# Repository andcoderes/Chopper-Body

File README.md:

# Chopper Body V2

## Acknowledgments

This firmware was strongly influenced by the [Amidala](https://github.com/thePunderWoman/Amidala) firmware by [thePunderWoman](https://github.com/thePunderWoman).

ESP32-based body controller for the Chopper robot. Controls drive motors, dome rotation, body servos, MP3 audio, and a bubble machine via ESP-NOW commands from the controller.

## Features

- **MDDS30 drive motors** — PWM Independent mode, differential steering
- **Cytron MD10C dome rotation** — bidirectional speed control
- **Pololu Maestro servos** — scripted body animations via Serial1
- **MP3 audio player** — serial protocol playback via Serial2
- **Bubbles relay** — on/off control
- **ESP-NOW** — encrypted communication with the controller
- **WiFi AP + OTA** — web interface at `chopper.body` for firmware updates
- **Safety timeout** — motors stop after 500ms without commands or on ESP-NOW disconnect

## ESP32 Pin Assignments

| Function | GPIO | Type | Notes |
|---|---|---|---|
| **MDDS30 IN1** (left dir) | 4 | Digital out | LOW = forward, HIGH = reverse. 10k pull-down on board |
| **MDDS30 AN1** (left speed) | 17 | LEDC PWM | 5 kHz, 8-bit. 10k pull-down on board |
| **MDDS30 IN2** (right dir) | 16 | Digital out | LOW = forward, HIGH = reverse. 10k pull-down on board |
| **MDDS30 AN2** (right speed) | 5 | LEDC PWM | 5 kHz, 8-bit. 10k pull-down on board |
| **Cytron MD10C DIR** (dome dir) | 14 | Digital out | 10k pull-down on board |
| **Cytron MD10C PWM** (dome speed) | 27 | LEDC PWM | 5 kHz, 8-bit. 10k pull-down on board |
| **Dome home sensor** | 26 | Digital in | A3144 hall-effect, 10k+20k divider |
| **Dome encoder A** | 25 | Digital in | 10k+20k divider |
| **Dome encoder B** | 33 | Digital in | 10k+20k divider |
| **Pololu Maestro TX** | 32 | Serial1 TX | 9600 baud |
| **Pololu Maestro RX** | 35 | Serial1 RX | Input-only. 1k + 2k voltage divider (5V -> 3.3V) |
| **MP3 Player TX** | 19 | Serial2 TX | 9600 baud |
| **MP3 Player RX** | 18 | Serial2 RX | 1k + 2k voltage divider (5V -> 3.3V) |
| **Bubbles relay** | 21 | Digital out | Relay module, active HIGH |
| **USB Debug TX** | 1 | Serial0 TX | 115200 baud |
| **USB Debug RX** | 3 | Serial0 RX | 115200 baud |

GPIO12 and GPIO13 (previously used for MDDS30) are intentionally left
unconnected — GPIO12 is an ESP32 boot-strapping pin (flash voltage select)
and stray HIGH signals on it during power-up can put the board in a reset
loop. GPIO22/23 (previously Maestro) and GPIO34 (previously dome encoder B)
are also now unused.

### MDDS30 DIP Switch Setting

`0b10110100` — PWM Independent mode. All three hardware UARTs remain free.

### Serial Port Allocation

| UART | GPIO TX | GPIO RX | Baud | Device |
|---|---|---|---|---|
| Serial0 | 1 | 3 | 115200 | USB debug console |
| Serial1 | 32 | 35 | 9600 | Pololu Maestro servo controller |
| Serial2 | 19 | 18 | 9600 | MP3 player module (Catalex-style, requires "select TF card" init) |

## Build

Requires [PlatformIO](https://platformio.org/).

Before your first build, set up ESP-NOW encryption keys — see
[Generating ESP-NOW keys](#generating-esp-now-keys) below. The build will
fail with a clear error if `.env` is missing.

```bash
# One-time setup: copy the template and fill in real keys
cp .env.example .env

# Compile firmware
pio run

# Upload to ESP32
pio run --target upload

# Run unit tests (native)
pio test -e native

# Monitor serial output
pio device monitor
```

## Project Structure

```
pcb/                                  # KiCad project (schematic, board, gerbers)
firmware/
  platformio.ini
  .env.example                       # Template for ESP-NOW keys — copy to .env
  partitions/ota_4MB.csv
  scripts/load_secrets.py            # Pre-build: .env -> include/secrets.h
  scripts/embed_web.py              # Pre-build: inlines CSS into HTML
  web/
    assets/common.css                # Shared styles
    index.html                       # Home page (info + links)
    update.html                      # OTA firmware upload page
  include/
    web_pages.h                      # AUTO-GENERATED by embed_web.py
    secrets.h                        # AUTO-GENERATED by load_secrets.py, gitignored
  src/
    config.h                         # Pin definitions, timeouts (keys come from secrets.h)
    main.cpp                         # Setup/loop, WiFi, command dispatch
    communication/
      MessageTypes.h                 # BodyCommand / BodyTelemetry structs
      EspNowController.h/.cpp        # ESP-NOW encrypted communication
    motor/
      MotorController.h/.cpp         # MDDS30 + L298N motor control
    servo/
      ServoController.h/.cpp         # Pololu Maestro body servos
    audio/
      AudioController.h/.cpp         # Serial MP3 player protocol
    web/
      WebController.h/.cpp           # WiFi AP, OTA updates, info API
      logger.h                       # Serial logging utility
  test/
    mocks/                           # Arduino/ESP32 mock headers
    test_message_types/              # Struct packing and field tests
    test_motor_controller/           # Drive mixing, dome, timeout tests
    test_audio_controller/           # MP3 protocol frame tests
    test_servo_controller/           # Animation state machine tests
    test_esp_now_controller/         # Connection timeout, dispatch tests
```

## ESP-NOW Protocol

### Controller -> Body (msgType = 3, 26 bytes)

| Field | Type | Description |
|---|---|---|
| msgType | int8 | Always 3 |
| status | int8 | 0 = buttons, 1 = movement, 2 = settings, -1 = connection |
| lx | int8 | Drive X axis: -100 to 100 |
| ly | int8 | Drive Y axis: -100 to 100 |
| domeSpeed | int8 | Dome rotation: -100 to 100 |
| audioTrack | uint8 | 0 = none, 1-255 = play track |
| volume | uint8 | 0-30 |
| bubbles | uint8 | 0 = off, 1 = on |
| button | char[8] | Servo button name (e.g. "y", "du") |
| macro | int16[4] | Servo macro IDs |
| connectionStatus | int8 | 0 = disconnected, 1 = connected |
| padding | uint8 | Alignment padding |

### Body -> Controller (msgType = 4, 8 bytes)

| Field | Type | Description |
|---|---|---|
| msgType | int8 | Always 4 |
| connected | uint8 | 1 if ESP-NOW link active |
| motorsActive | uint8 | 1 if drive/dome motors running |
| audioPlaying | uint8 | 1 if audio track playing |
| uptimeMs | uint32 | Milliseconds since boot |

## WiFi Access Point

- **SSID:** ChopperBody
- **IP:** 192.168.5.1
- **mDNS:** chopper-body.local
- **Pages:** `/` (home), `/update` (OTA)
- **API:** `/api/info` (JSON: version, uptime, heap, MAC)

## Generating ESP-NOW keys

This board talks to the other Chopper boards over encrypted ESP-NOW. Before
your first build, generate two 16-byte (128-bit) keys — a Primary Master Key
(PMK) and a Local Master Key (LMK) — and put them in a `.env` file
(gitignored, never commit it) at the project root:

```bash
cp .env.example .env
```

Generate two random 16-byte keys, each as 32 hex characters:

```bash
# Option 1: openssl
openssl rand -hex 16   # run twice — once for PMK_KEY, once for LMK_KEY

# Option 2: python
python3 -c "import secrets; print(secrets.token_hex(16))"
```

Edit `.env` and paste the values in:

```
PMK_KEY=<first random hex string>
LMK_KEY=<second random hex string>
```

**These two keys must be byte-for-byte identical across chopper body,
chopper head, and chopper receiver** — generate them once and copy the same
`.env` values into all three projects. Mismatched keys mean the boards can't
decrypt each other's ESP-NOW packets and the mesh will never connect.

`.env` also holds `CONTROLLER_MAC` — the controller's WiFi MAC address (as
hex, e.g. `C0CDD6CA29E0`), which must likewise be identical across all three
firmware projects — and `WIFI_AP_PASSWORD`, the password for this board's
local OTA-update access point (pick your own, at least 8 characters; unlike
the other values, this one doesn't need to match the other boards).

`scripts/load_secrets.py` runs automatically before every build (see
`platformio.ini`) and turns `.env` into `include/secrets.h`, which
`config.h` includes. Neither `.env` nor the generated `secrets.h` are
committed to git — the build fails with a clear error if `.env` is missing.

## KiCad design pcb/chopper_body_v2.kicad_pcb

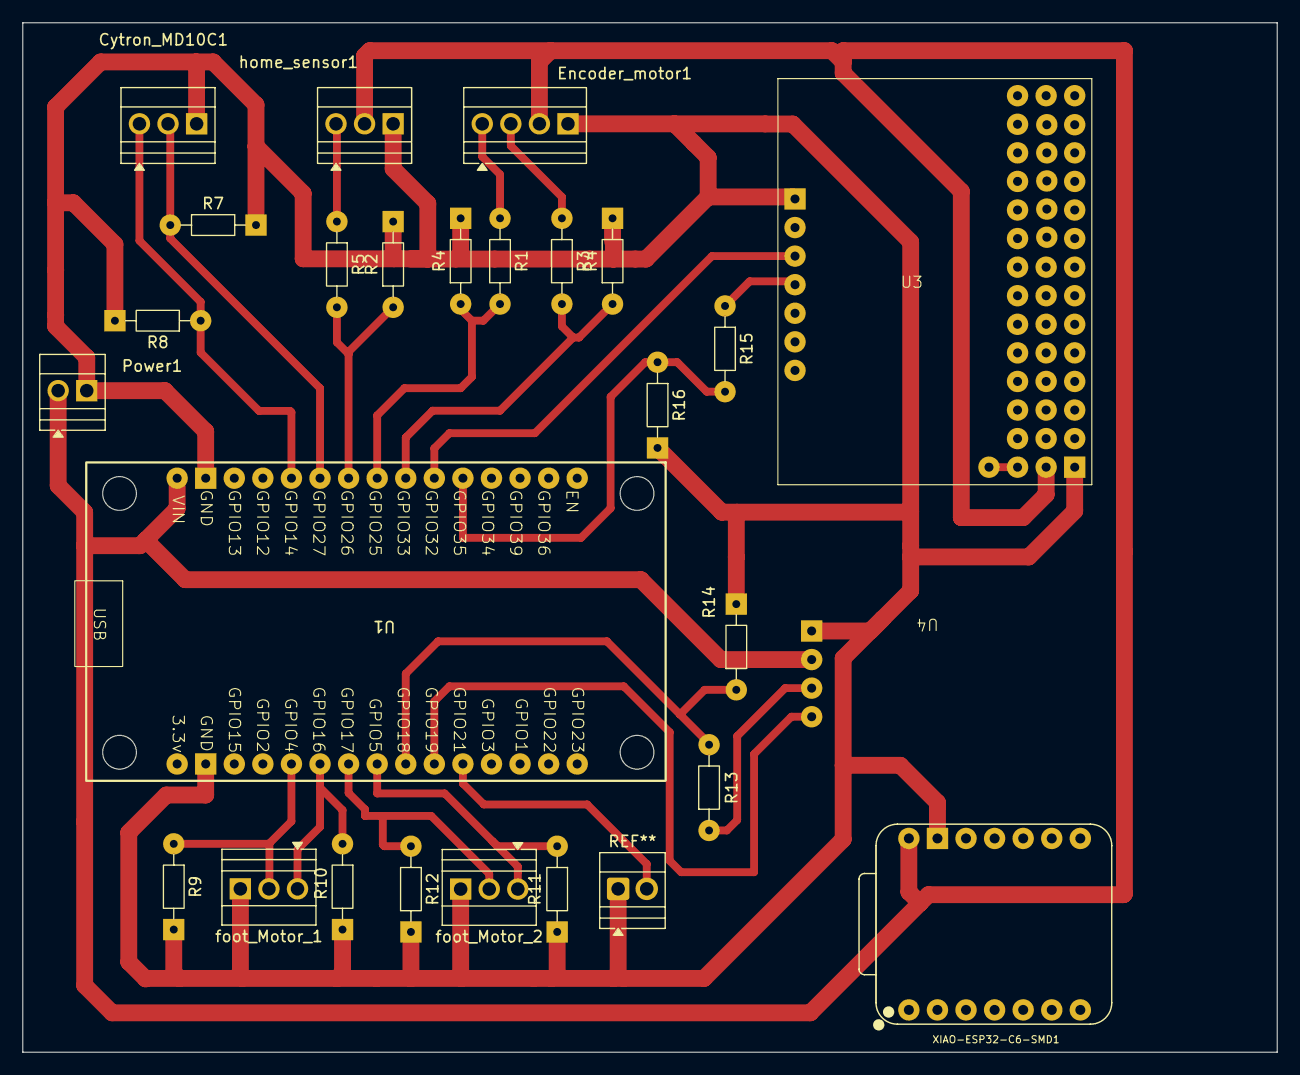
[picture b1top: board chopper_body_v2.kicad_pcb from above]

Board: 2 copper layers, 111.5 x 91.5 mm, 26 parts (0 on the bottom side), 21 nets.

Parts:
Cytron_MD10C1: DIR_PWM_GND; TerminalBlock_Xinya_XY308-2.54-3P_1x03_P2.54mm_Horizontal
Encoder_motor1: motor_head_enc_a_enc_b_5v_GND; TerminalBlock_Xinya_XY308-2.54-4P_1x04_P2.54mm_Horizontal
Power1: 5v_GND; TerminalBlock_Xinya_XY308-2.54-2P_1x02_P2.54mm_Horizontal
R1, R3, R5, R7, R8, R9, R10, R11, R12: 10K; R_Axial_DIN0204_L3.6mm_D1.6mm_P7.62mm_Horizontal
R2, R4, R4#2: 20K; R_Axial_DIN0204_L3.6mm_D1.6mm_P7.62mm_Horizontal
R13, R15: 1K; R_Axial_DIN0204_L3.6mm_D1.6mm_P7.62mm_Horizontal
R14, R16: 2K; R_Axial_DIN0204_L3.6mm_D1.6mm_P7.62mm_Horizontal
U1: ESP32_30pin
U3: Pololu_Maestro_12
U4: audio_trigger
XIAO-ESP32-C6-SMD1: XIAO-ESP32-C6-SMD; XIAO-ESP32-C6-DIP
foot_Motor_1: IN1_IN2_GND; TerminalBlock_Xinya_XY308-2.54-3P_1x03_P2.54mm_Horizontal
foot_Motor_2: AN1_IN1_GND; TerminalBlock_Xinya_XY308-2.54-3P_1x03_P2.54mm_Horizontal
home_sensor1: sensor_5v_GND; TerminalBlock_Xinya_XY308-2.54-3P_1x03_P2.54mm_Horizontal

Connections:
+5V: Encoder_motor1.3, Power1.1, U1.1 (VIN), U3.V5In, U4.5V, XIAO-ESP32-C6-SMD1.14 (VBUS), home_sensor1.2
AN1: R12.1, U1.22 (GPIO17), foot_Motor_2.2
AN2: R11.1, U1.23 (GPIO5), foot_Motor_2.1
GND: Cytron_MD10C1.3, Encoder_motor1.4, Power1.2, R2.2, R4.2, R4#2.2, R7.2, R8.2, R9.2, R10.2, R11.2, R12.2, R14.2, R16.2, U1.2 (GND), U1.17 (GND), U3.GNDBoard, U3.GNDIn, U4.GND, XIAO-ESP32-C6-SMD1.13 (GND), foot_Motor_1.3, foot_Motor_2.3, home_sensor1.3
IN1: R9.1, U1.20 (GPIO4), foot_Motor_1.2
IN2: R10.1, U1.21 (GPIO16), foot_Motor_1.1
MD10PWM: Cytron_MD10C1.2, R7.1, U1.6 (GPIO27)
MD10_DIR: Cytron_MD10C1.1, R8.1, U1.5 (GPIO14)
audio_rx: U1.25 (GPIO19), U4.RX
audio_tx: R13.1, U4.TX
audio_tx_resistor: R13.2, R14.1, U1.24 (GPIO18)
encoder_a_resistor: R1.2, R4#2.1, U1.8 (GPIO25)
encoder_a_signal: Encoder_motor1.1, R1.1
encoder_b_resistor: R3.2, R4.1, U1.9 (GPIO33)
encoder_b_signal: Encoder_motor1.2, R3.1
home_sensor_resistant: R2.1, R5.2, U1.7 (GPIO26)
home_sensor_signal: R5.1, home_sensor1.1
pololu_rx: U1.10 (GPIO32), U3.Rx
pololu_tx: R15.1, U3.Tx
pololu_tx_resistor: R15.2, R16.1, U1.11 (GPIO35)
vin_pololu: U3.VSRV, U3.vin
